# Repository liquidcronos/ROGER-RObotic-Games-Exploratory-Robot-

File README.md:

# Roger

Dokumenation und Code des RObotic Games Exploratory Robot (ROGER) welcher am ehemaligen [Lehrstuhl für Automation](http://proaut.ziti.uni-heidelberg.de/joomla/index.php/en/) konzipiert und gebaut wurde für die Vorlesung Robotic Games.

|Kontributionen:||
|:---:|:---:|
|Jens Wagner| Design der Platine und Ansteuerung der Sensoren und Motoren|
|Tobias Bak | Hardwaredesign und zusammenbau |
|Jan Baumgärnter| Odometrie und höhere Verhalten|

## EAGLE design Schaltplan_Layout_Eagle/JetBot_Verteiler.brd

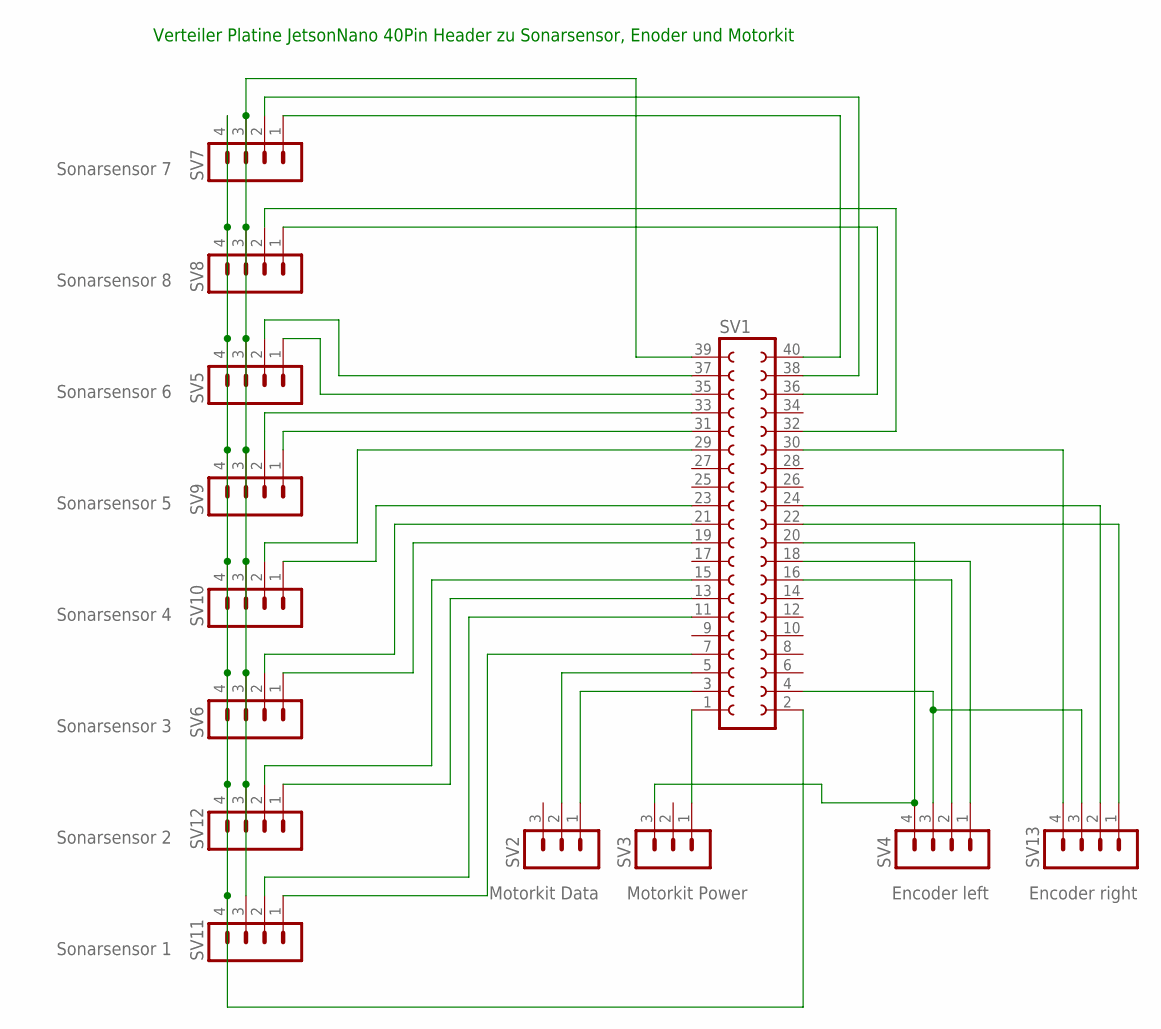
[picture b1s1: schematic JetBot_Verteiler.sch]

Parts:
SV1: FE20-2
SV2: Motorkit Data; MA03-1
SV3: Motorkit Power; MA03-1
SV4: Encoder left; MA04-1
SV5: Sonarsensor 6; MA04-1
SV6: Sonarsensor 3; MA04-1
SV7: Sonarsensor 7; MA04-1
SV8: Sonarsensor 8; MA04-1
SV9: Sonarsensor 5; MA04-1
SV10: Sonarsensor 4; MA04-1
SV11: Sonarsensor 1; MA04-1
SV12: Sonarsensor 2; MA04-1
SV13: Encoder right; MA04-1

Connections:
unnamed: SV1.1, SV3.1
unnamed: SV1.3, SV2.1
unnamed: SV1.5, SV2.2
unnamed: SV1.24, SV13.2
unnamed: SV1.20, SV3.3, SV4.4
unnamed: SV1.7, SV11.1
unnamed: SV1.2, SV5.4, SV6.4, SV7.4, SV8.4, SV9.4, SV10.4, SV11.4, SV12.4
unnamed: SV1.11, SV11.2
unnamed: SV1.13, SV12.1
unnamed: SV1.15, SV12.2
unnamed: SV1.37, SV5.2
unnamed: SV1.29, SV10.2
unnamed: SV1.32, SV8.2
unnamed: SV1.33, SV9.2
unnamed: SV1.19, SV6.1
unnamed: SV1.21, SV6.2
unnamed: SV1.23, SV10.1
unnamed: SV1.31, SV9.1
unnamed: SV1.40, SV7.1
unnamed: SV1.38, SV7.2
unnamed: SV1.4, SV4.3, SV13.3
unnamed: SV1.16, SV4.2
unnamed: SV1.18, SV4.1
unnamed: SV1.35, SV5.1
unnamed: SV1.22, SV13.1
unnamed: SV1.36, SV8.1
unnamed: SV1.39, SV5.3, SV6.3, SV7.3, SV8.3, SV9.3, SV10.3, SV11.3, SV12.3
unnamed: SV1.30, SV13.4

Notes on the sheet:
Verteiler Platine JetsonNano 40Pin Header zu Sonarsensor, Enoder und Motorkit

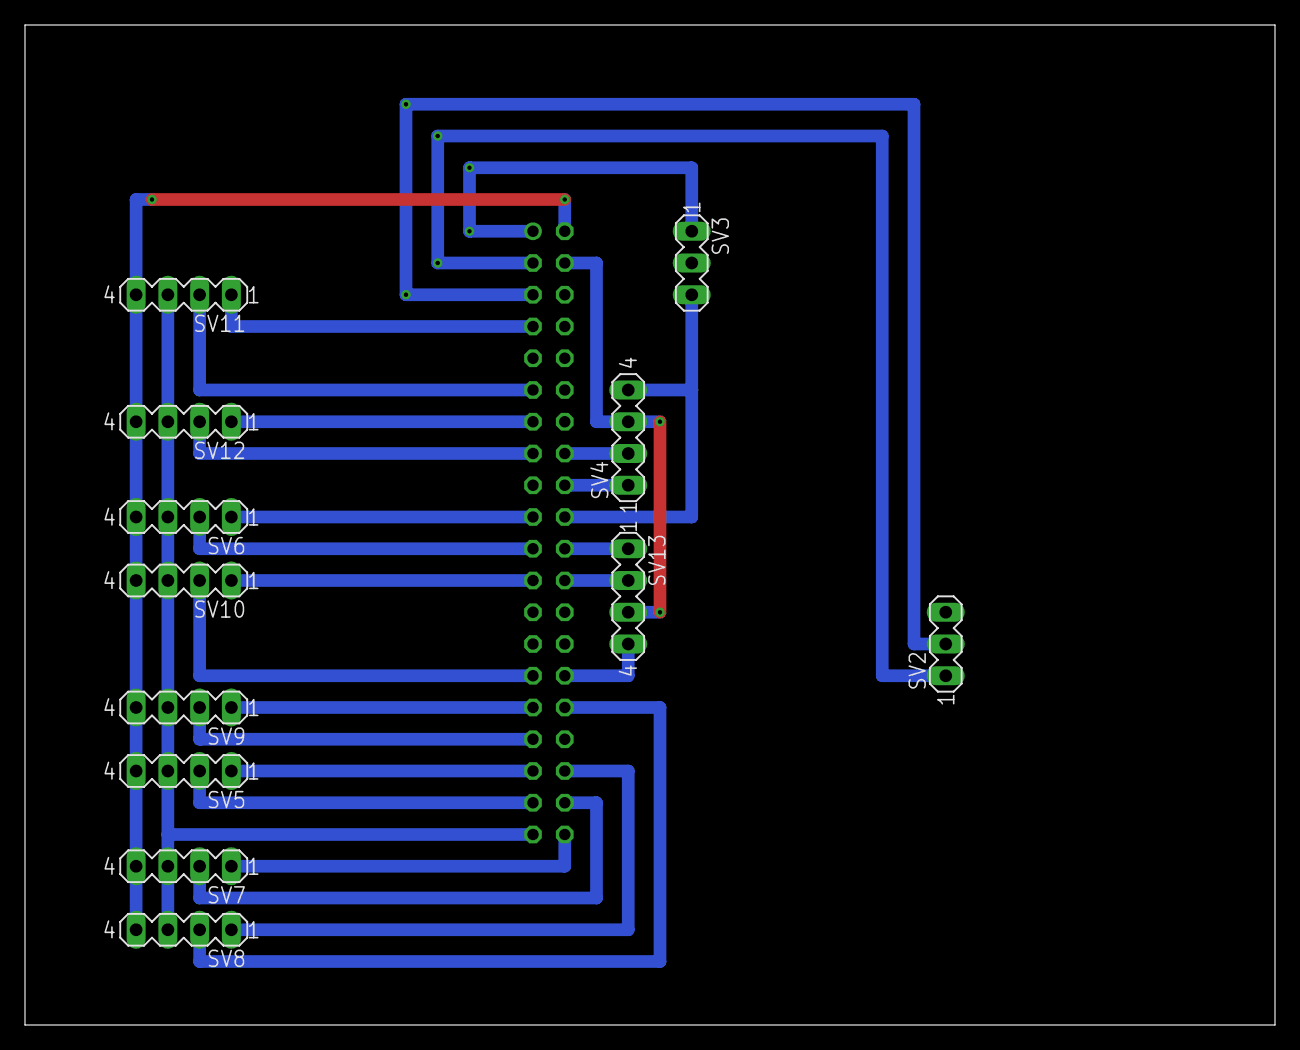
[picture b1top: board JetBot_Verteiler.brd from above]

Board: 2 copper layers, 100.0 x 80.0 mm, 13 parts (1 on the bottom side), 28 nets.

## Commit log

2019-09-26 added robot level control
2019-09-26 added dead reckoning
2019-09-26 collected all robot measurments in single file
2019-09-26 added homing
2019-09-26 added collision avoidance
2019-09-27 build functional package
2019-09-27 startet sonar read out
2019-10-01 added multithreading prototype to sonar_readout
2019-10-01 added optional pos bottleneck
2019-10-02 finished laser to sonar conversion
2020-09-20 moved from proaut internal git
2020-09-20 deleted scripts as duplicate
2020-10-17 added logo
2020-10-17 Update Roger_white.png
    added font to header
